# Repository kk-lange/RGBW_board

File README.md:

# RGBW_board

- *KiCAD* VER. *4.0.7*

## Description

PCB for adding support fir controlling high current RGBW LED strips. Constructed as aadd-on board for the WeMOS ESP-8266 development boards. supplied with a 12V wall-adptor

## Project relations

1. Standalone

## Re/-Versions table
- **Rev2**
- **Rev1**
- **Rev0**

## TODO
*Things to add in future Re/-Versions.*

- [x] Change pin-layout to MCU board 
- [x] Add support for 24V white LED strip
- [x] Change overall PCB layout
- [x] Change pin-layout (again) To fit new configuration og main ATmega board
- [x] Change position og DC-jack (Snap off if not used)
- [x] Edited silk-mask revision
- [ ] Add pull-up resistors on BTN input

### Authors
- Kenneth Konstmann-Lange

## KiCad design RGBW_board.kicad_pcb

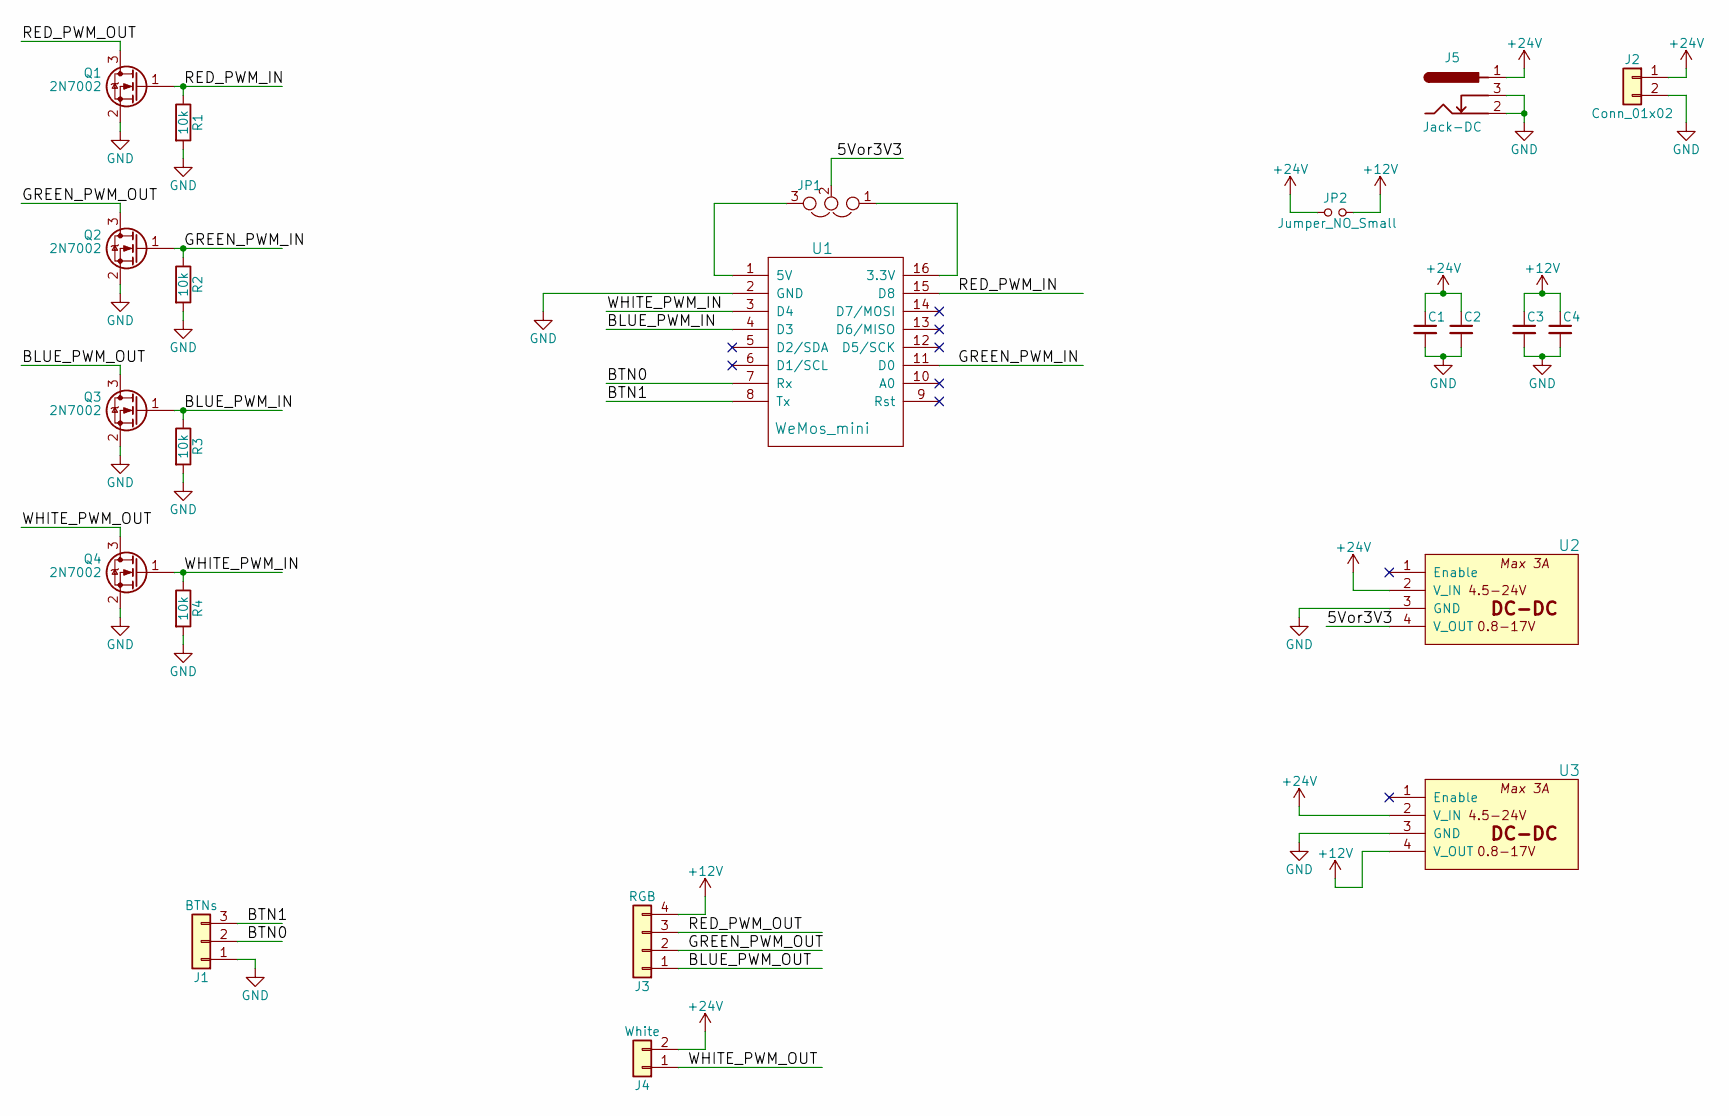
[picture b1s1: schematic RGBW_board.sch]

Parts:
C1, C2, C3, C4: C_Small; C_1210
J1: BTNs; Molex_KK-6410-03_03x2.54mm_Straight
J2: Conn_01x02; Battery_wirePad_SMD
J3: RGB; Molex_KK-6410-04_04x2.54mm_Straight
J4: White; Molex_KK-6410-02_02x2.54mm_Straight
J5: Jack-DC; BARREL_JACK
JP1: Jumper_NC_Dual; Jumper_dual
JP2: Jumper_NO_Small; R_0805
Q1, Q2, Q3, Q4: 2N7002; SOT-23
R1, R2, R3, R4: 10k; R_0805
U1: WeMos_mini; wemos-d1-mini-with-pin-header
U2, U3: Mini_DC-DC_4.5-24V_to_0.8-17V; Mini_DC-DC_converter_RED

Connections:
+12V: C3.1, C4.1, J3.4, JP2.2, U3.4 (V_OUT)
+24V: C1.1, C2.1, J2.1, J4.2, J5.1, JP2.1, U2.2 (V_IN), U3.2 (V_IN)
/5Vor3V3: JP1.2, U2.4 (V_OUT)
/BLUE_PWM_IN: Q3.1 (G), R3.1, U1.4 (D3)
/BLUE_PWM_OUT: J3.1, Q3.3 (D)
/BTN0: J1.2, U1.7 (Rx)
/BTN1: J1.3, U1.8 (Tx)
/GREEN_PWM_IN: Q2.1 (G), R2.1, U1.11 (D0)
/GREEN_PWM_OUT: J3.2, Q2.3 (D)
/RED_PWM_IN: Q1.1 (G), R1.1, U1.15 (D8)
/RED_PWM_OUT: J3.3, Q1.3 (D)
/WHITE_PWM_IN: Q4.1 (G), R4.1, U1.3 (D4)
/WHITE_PWM_OUT: J4.1, Q4.3 (D)
GND: C1.2, C2.2, C3.2, C4.2, J1.1, J2.2, J5.2, J5.3, Q1.2 (S), Q2.2 (S), Q3.2 (S), Q4.2 (S), R1.2, R2.2, R3.2, R4.2, U1.2 (GND), U2.3 (GND), U3.3 (GND)
unnamed: JP1.1, U1.16 (3.3V)
unnamed: JP1.3, U1.1 (5V)

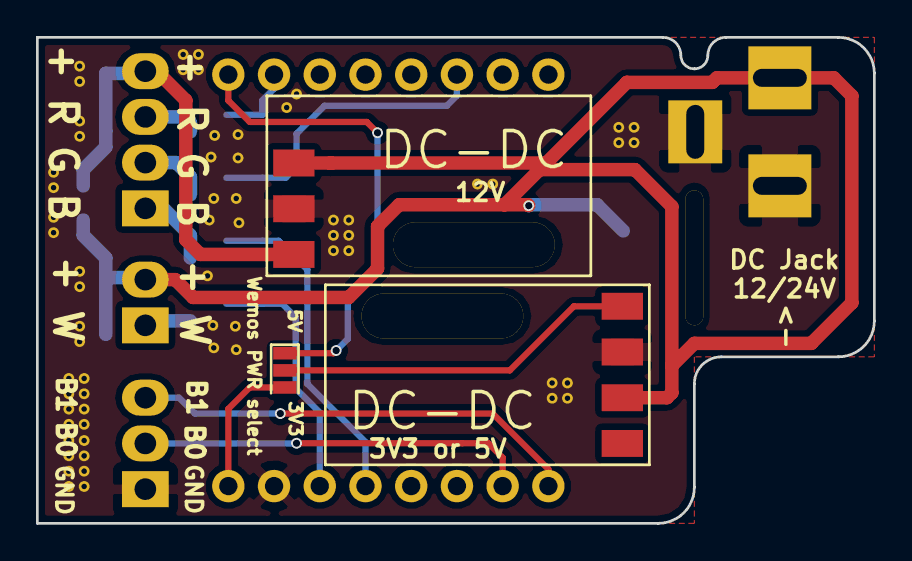
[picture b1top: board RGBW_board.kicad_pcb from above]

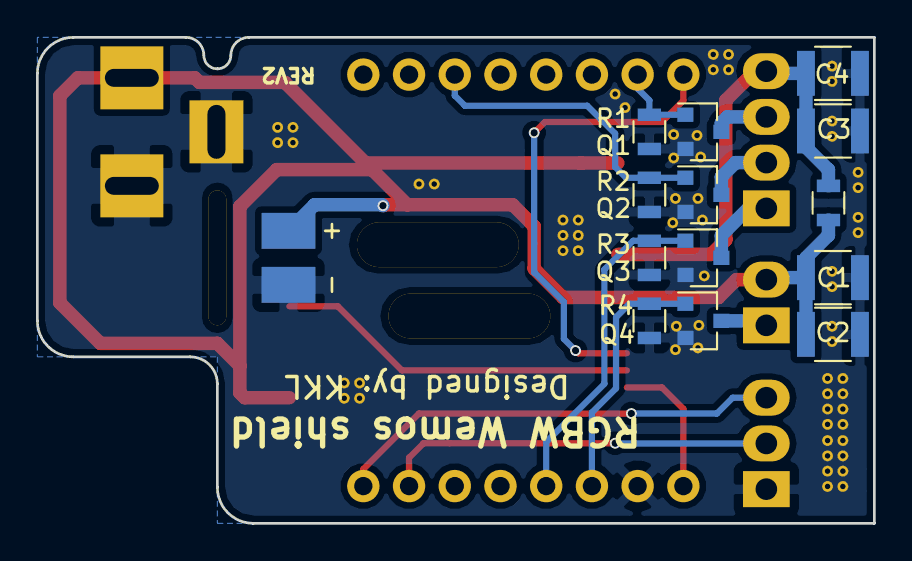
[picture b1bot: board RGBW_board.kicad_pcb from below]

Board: 2 copper layers, 46.5 x 27.0 mm, 22 parts (15 on the bottom side), 16 nets.

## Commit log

2020-02-14 Init Commit
2020-02-14 --REV0-- Added rev0 of project to git
2020-02-14 --REV0-- Updated READMED file
2020-02-14 --REV1-- Added rev1 to project git
2020-02-14 Updated README file
2020-02-14 --REV2-- Added rev2 to git project
2020-02-14 --REV2-- Updated README file
2020-02-14 --REV2-- Change Revision on silkscreen
